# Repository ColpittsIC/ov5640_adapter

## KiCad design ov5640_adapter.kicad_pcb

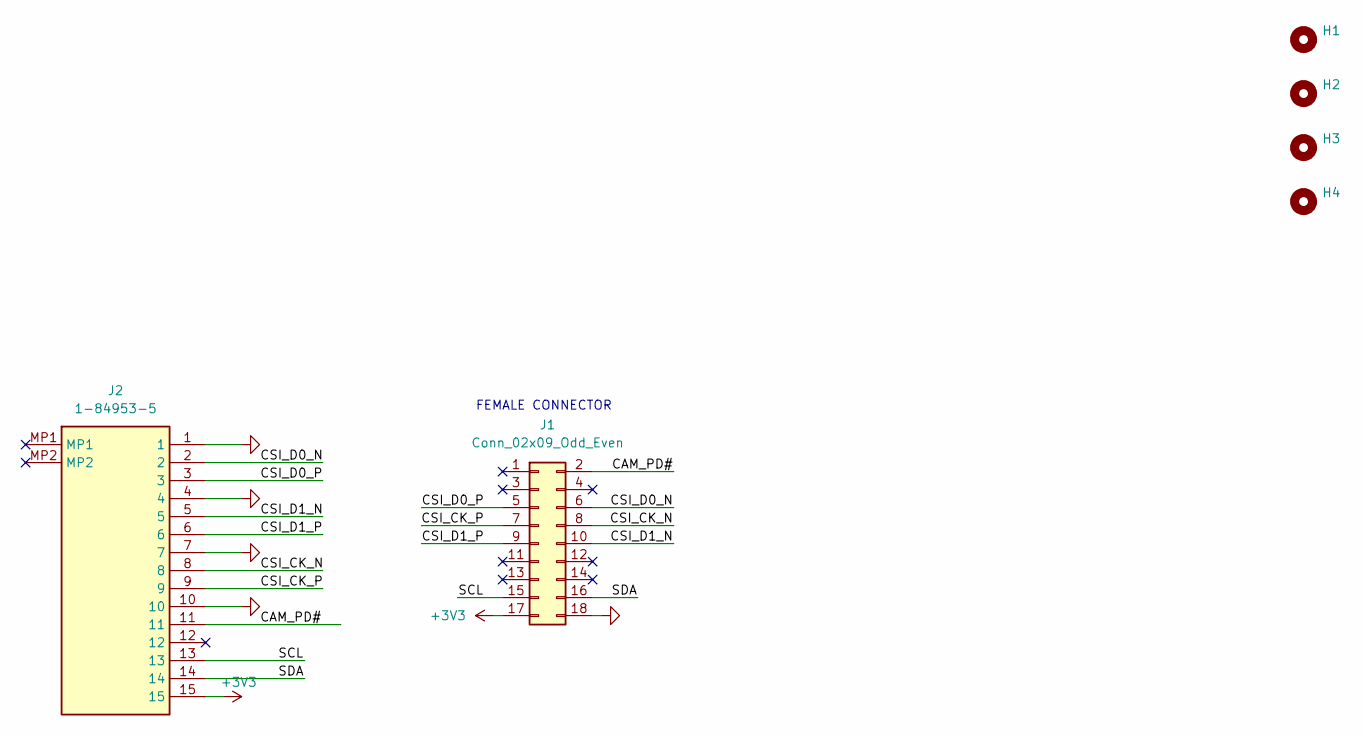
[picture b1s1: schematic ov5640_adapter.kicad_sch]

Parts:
H1, H2, H3, H4: MountingHole; MountingHole_3mm
J1: Conn_02x09_Odd_Even; PinSocket_2x09_P2.54mm_Vertical
J2: 1-84953-5; Mouser Part Number 571-1-84953-5

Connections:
+3V3: J1.17, J2.15
/CAM_PD#: J1.2, J2.11
/CSI_CK_N: J1.8, J2.8
/CSI_CK_P: J1.7, J2.9
/CSI_D0_N: J1.6, J2.2
/CSI_D0_P: J1.5, J2.3
/CSI_D1_N: J1.10, J2.5
/CSI_D1_P: J1.9, J2.6
/SCL: J1.15, J2.13
/SDA: J1.16, J2.14
GND: J1.18, J2.1, J2.4, J2.7, J2.10

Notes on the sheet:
FEMALE CONNECTOR

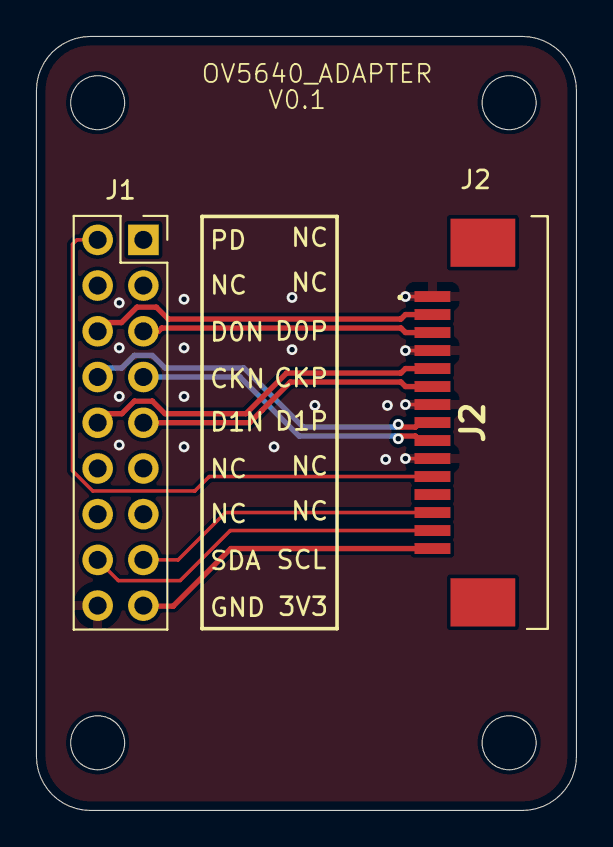
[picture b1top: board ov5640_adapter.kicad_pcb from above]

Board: 2 copper layers, 30.0 x 43.0 mm, 6 parts (0 on the bottom side), 11 nets.

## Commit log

2025-08-11 First Push
2025-08-11 Added Production files
